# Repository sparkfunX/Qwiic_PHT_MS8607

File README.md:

# Qwiic PHT Sensor MS8607

The TE MS8607 combined pressure, humidity and temperature sensor in Qwiic format.

[Qwiic PHT Sensor MS8607 (SPX-16298)](https://www.sparkfun.com/products/16298)

The MS8607 sensor is a self-contained pressure, humidity and temperature sensor that is fully calibrated during manufacture.
The sensor can operate from 1.5V to 3.6V. The MS8607 is ideal for weather station applications embedded into compact devices and
any applications in which pressure, humidity and temperature monitoring is required. The pressure sensor will operate down to
10mbar which is equivalent to an altitude of approx. 31,000m making it suitable for high altitude ballooning and other low pressure
applications.

## Specifications

- Operating pressure range: 10 to 2000 mbar
- Measures relative humidity from 0% to 100%
- Measures temperature from -40C to 85C
- Fast response time
- I2C communication
- Very low power consumption

## Repository Contents
- **/Hardware** - Eagle schematic and PCB design files
- **/Documents** - contains the TE datasheet
- **LICENSE.md** contains the licence information

## Library

- **[Arduino Library](https://github.com/sparkfun/SparkFun_PHT_MS8607_Arduino_Library)** - Library for reading pressure in mBar, altitude, etc.

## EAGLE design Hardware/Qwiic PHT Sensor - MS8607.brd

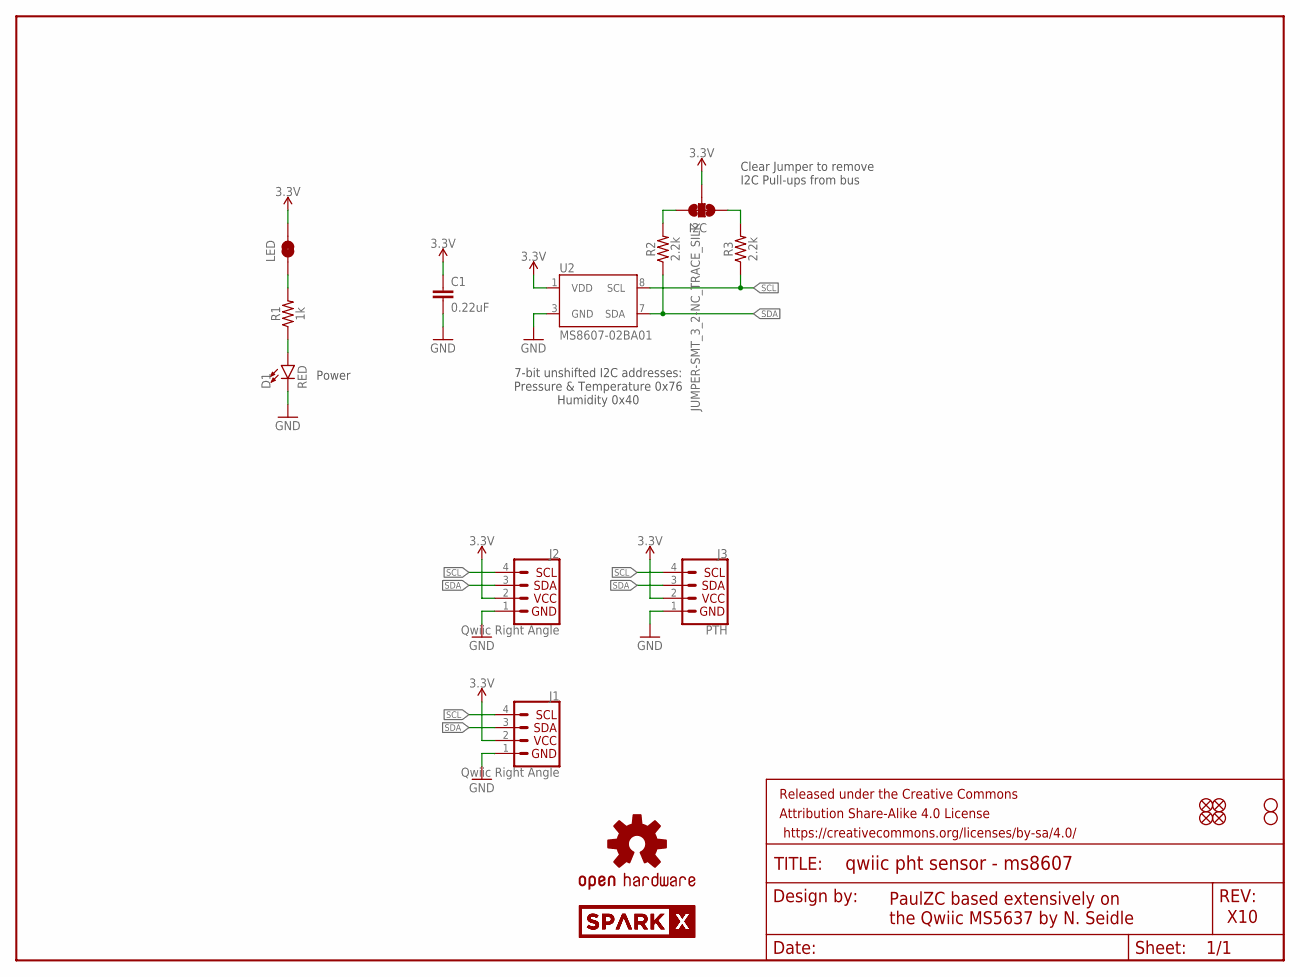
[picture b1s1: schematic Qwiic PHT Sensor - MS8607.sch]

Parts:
C1: 0.22uF; 0603
D1: RED; LED-0603
FRAME1: FRAME-LETTER; CREATIVE_COMMONS
I2C: JUMPER-SMT_3_2-NC_TRACE_SILK; SMT-JUMPER_3_2-NC_TRACE_SILK
J1, J2: Qwiic Right Angle; JST04_1MM_RA
J3: PTH; 1X04_NO_SILK
JP1, JP2, JP5, JP6: FIDUCIALUFIDUCIAL; MICRO-FIDUCIAL
JP3, JP4: STAND-OFF
LED: JUMPER-SMT_2_NC_TRACE_SILK; SMT-JUMPER_2_NC_TRACE_SILK
LOGO1: OSHW-LOGOMINI; OSHW-LOGO-MINI
R1: 1k; 0603
R2, R3: 2.2k; 0603
U2: MS8607-02BA01
U$1, U$2: SPARKX-LOGO4; SPARKX-MEDIUM

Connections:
3.3V: C1.1, I2C.2, J1.2, J2.2, J3.2 (VCC), LED.2, U2.1 (VDD)
GND: C1.2, D1.C, J1.1, J2.1, J3.1 (GND), U2.3 (GND)
unnamed: I2C.1, R3.2
unnamed: I2C.3, R2.2
unnamed: D1.A, R1.1
unnamed: LED.1, R1.2
SCL: J1.4, J2.4, J3.4 (SCL), R3.1, U2.8 (SCL)
SDA: J1.3, J2.3, J3.3 (SDA), R2.1, U2.7 (SDA)

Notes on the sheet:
PaulZC based extensively on the Qwiic MS5637 by N. Seidle
X10
7-bit unshifted I2C addresses: Pressure & Temperature 0x76 Humidity 0x40
Clear Jumper to remove I2C Pull-ups from bus
Power

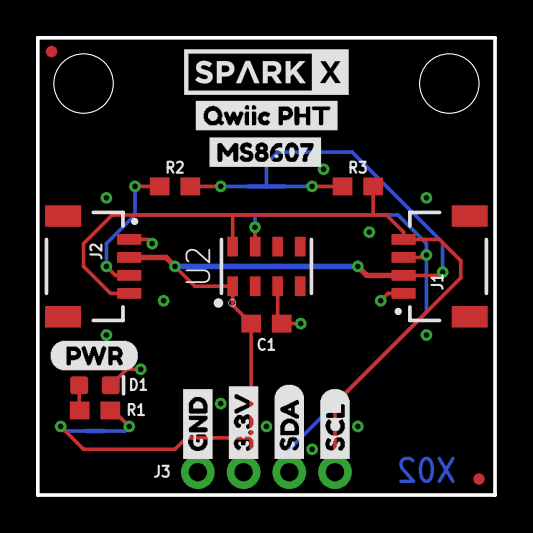
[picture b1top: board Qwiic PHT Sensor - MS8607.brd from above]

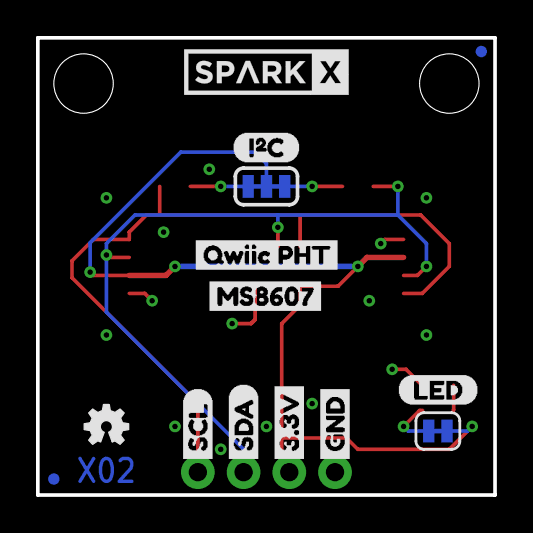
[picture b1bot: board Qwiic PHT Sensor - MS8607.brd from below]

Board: 2 copper layers, 25.4 x 25.4 mm, 36 parts (14 on the bottom side), 8 nets.

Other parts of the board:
U$3, U$22: GND1
U$4, U$21: 3#3V2
U$5, U$27: SDA8
U$6, U$26: SCL9
U$9, U$12: QWIIC_PHT0
U$10: (PWR)
U$11: (I_SUPER2_C)
U$15, U$16: MS86070
U$17: LED0

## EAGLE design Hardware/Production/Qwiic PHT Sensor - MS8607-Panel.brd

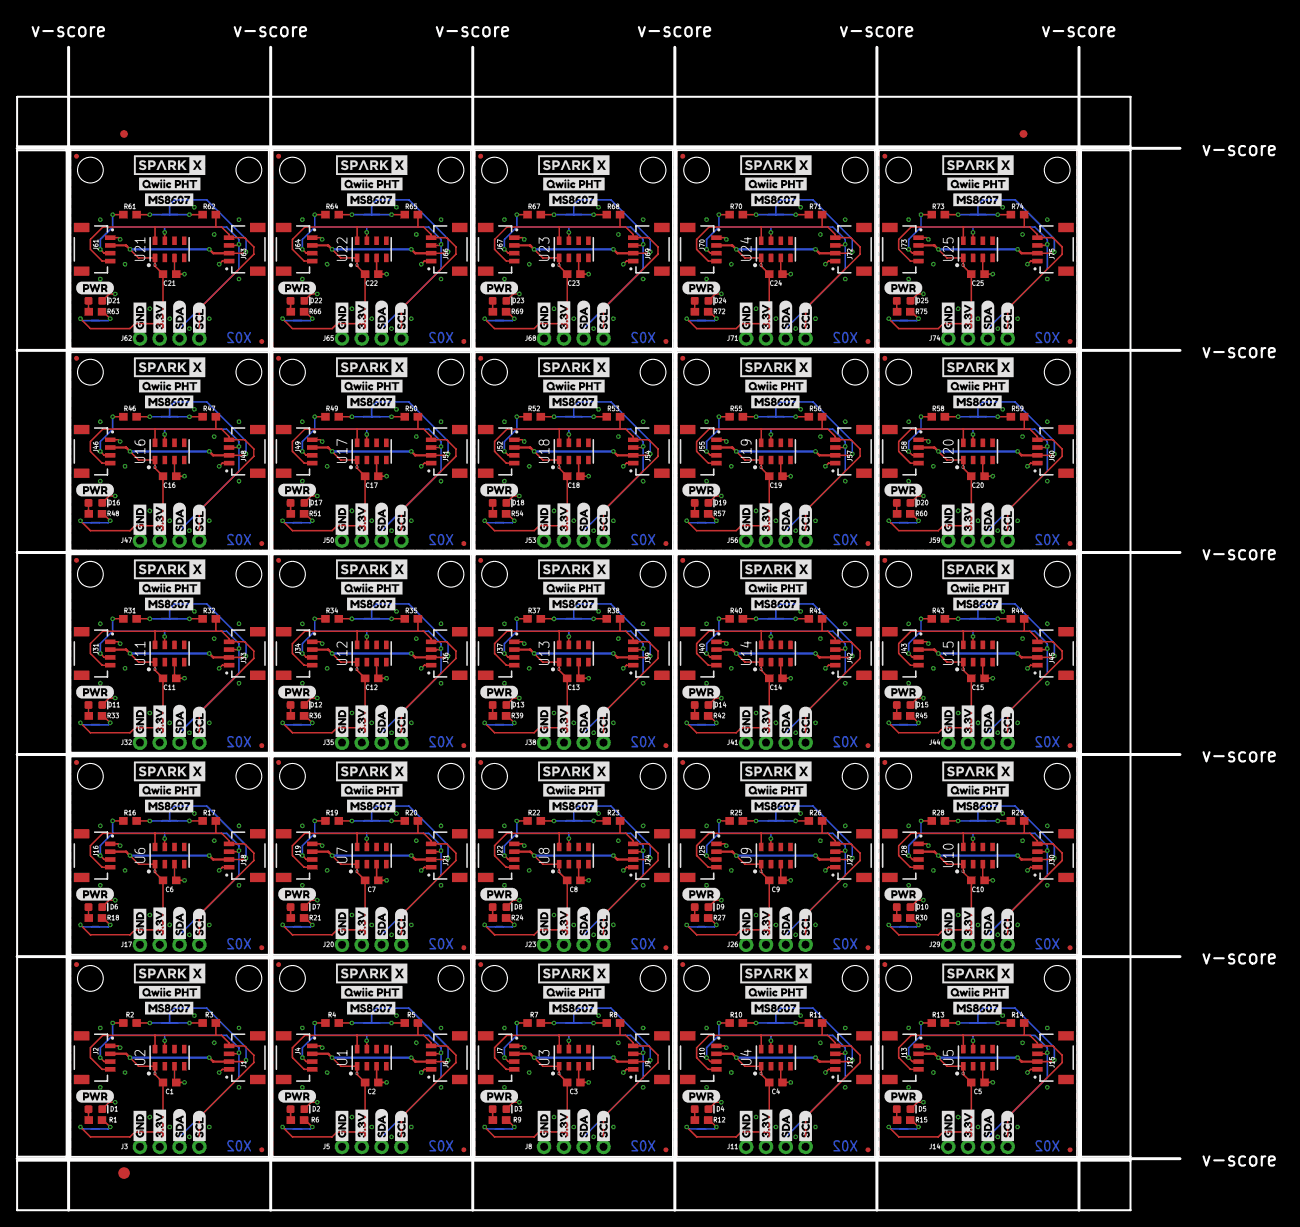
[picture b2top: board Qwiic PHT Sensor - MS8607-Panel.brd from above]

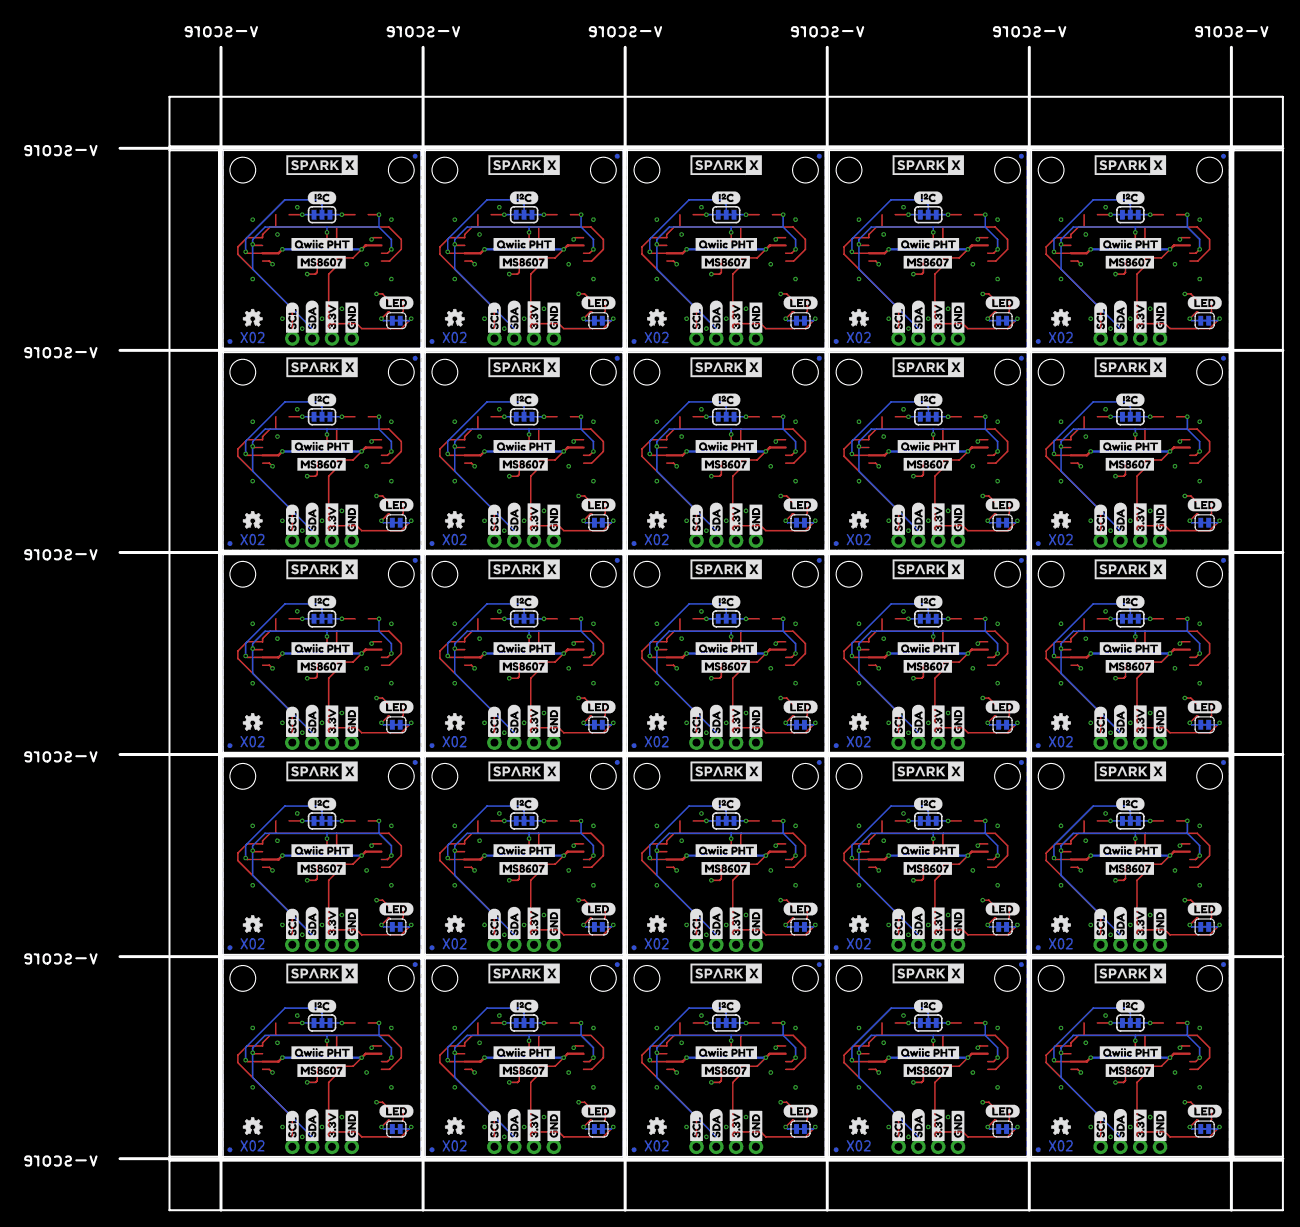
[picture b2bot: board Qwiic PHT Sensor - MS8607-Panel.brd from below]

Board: 2 copper layers, 162.3 x 153.0 mm, 878 parts (350 on the bottom side), 200 nets.

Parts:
C1, C2, C3, C4, C5, C6, C7, C8, C9, C10, C11, C12, C13, C14, C15, C16, C17, C18, C19, C20, C21, C22, C23, C24, C25: 0.22uF; 0603
D1, D2, D3, D4, D5, D6, D7, D8, D9, D10, D11, D12, D13, D14, D15, D16, D17, D18, D19, D20, D21, D22, D23, D24, D25: RED; LED-0603
E$1, E$2: FIDUCIAL-1X2
E$3: FIDUCIAL-1.5X3
I2C, I2C1, I2C2, I2C3, I2C4, I2C5, I2C6, I2C7, I2C8, I2C9, I2C10, I2C11, I2C12, I2C13, I2C14, I2C15, I2C16, I2C17, I2C18, I2C19, I2C20, I2C21, I2C22, I2C23, I2C24: JUMPER-SMT_3_2-NC_TRACE_SILK; SMT-JUMPER_3_2-NC_TRACE_SILK
J1, J2, J4, J6, J7, J9, J10, J12, J13, J15, J16, J18, J19, J21, J22, J24, J25, J27, J28, J30, J31, J33, J34, J36, J37, J39, J40, J42, J43, J45, J46, J48, J49, J51, J52, J54, J55, J57, J58, J60, J61, J63, J64, J66, J67, J69, J70, J72, J73, J75: Qwiic Right Angle; JST04_1MM_RA
J3, J5, J8, J11, J14, J17, J20, J23, J26, J29, J32, J35, J38, J41, J44, J47, J50, J53, J56, J59, J62, J65, J68, J71, J74: PTH; 1X04_NO_SILK
JP1, JP2, JP5, JP6, JP9, JP10, JP11, JP12, JP15, JP16, JP17, JP18, JP21, JP22, JP23, JP24, JP27, JP28, JP29, JP30, JP33, JP34, JP35, JP36, JP39, JP40, JP41, JP42, JP45, JP46, JP47, JP48, JP51, JP52, JP53, JP54, JP57, JP58, JP59, JP60, JP63, JP64, JP65, JP66, JP69, JP70, JP71, JP72, JP75, JP76, JP77, JP78, JP81, JP82, JP83, JP84, JP87, JP88, JP89, JP90, JP93, JP94, JP95, JP96, JP99, JP100, JP101, JP102, JP105, JP106, JP107, JP108, JP111, JP112, JP113, JP114, JP117, JP118, JP119, JP120, JP123, JP124, JP125, JP126, JP129, JP130, JP131, JP132, JP135, JP136, JP137, JP138, JP141, JP142, JP143, JP144, JP147, JP148, JP149, JP150: FIDUCIALUFIDUCIAL; MICRO-FIDUCIAL
JP3, JP4, JP7, JP8, JP13, JP14, JP19, JP20, JP25, JP26, JP31, JP32, JP37, JP38, JP43, JP44, JP49, JP50, JP55, JP56, JP61, JP62, JP67, JP68, JP73, JP74, JP79, JP80, JP85, JP86, JP91, JP92, JP97, JP98, JP103, JP104, JP109, JP110, JP115, JP116, JP121, JP122, JP127, JP128, JP133, JP134, JP139, JP140, JP145, JP146: STAND-OFF
LED, LED1, LED2, LED3, LED4, LED5, LED6, LED7, LED8, LED9, LED10, LED11, LED12, LED13, LED14, LED15, LED16, LED17, LED18, LED19, LED20, LED21, LED22, LED23, LED24: JUMPER-SMT_2_NC_TRACE_SILK; SMT-JUMPER_2_NC_TRACE_SILK
LOGO1, LOGO2, LOGO3, LOGO4, LOGO5, LOGO6, LOGO7, LOGO8, LOGO9, LOGO10, LOGO11, LOGO12, LOGO13, LOGO14, LOGO15, LOGO16, LOGO17, LOGO18, LOGO19, LOGO20, LOGO21, LOGO22, LOGO23, LOGO24, LOGO25: OSHW-LOGOMINI; OSHW-LOGO-MINI
R1, R6, R9, R12, R15, R18, R21, R24, R27, R30, R33, R36, R39, R42, R45, R48, R51, R54, R57, R60, R63, R66, R69, R72, R75: 1k; 0603
R2, R3, R4, R5, R7, R8, R10, R11, R13, R14, R16, R17, R19, R20, R22, R23, R25, R26, R28, R29, R31, R32, R34, R35, R37, R38, R40, R41, R43, R44, R46, R47, R49, R50, R52, R53, R55, R56, R58, R59, R61, R62, R64, R65, R67, R68, R70, R71, R73, R74: 2.2k; 0603
U1, U2, U3, U4, U5, U6, U7, U8, U9, U10, U11, U12, U13, U14, U15, U16, U17, U18, U19, U20, U21, U22, U23, U24, U25: MS8607-02BA01
U$1, U$2, U$7, U$8, U$35, U$36, U$52, U$53, U$69, U$70, U$86, U$87, U$103, U$104, U$120, U$121, U$137, U$138, U$154, U$155, U$171, U$172, U$188, U$189, U$205, U$206, U$222, U$223, U$239, U$240, U$256, U$257, U$273, U$274, U$290, U$291, U$307, U$308, U$324, U$325, U$341, U$342, U$358, U$359, U$375, U$376, U$392, U$393, U$409, U$410: SPARKX-LOGO4; SPARKX-MEDIUM
U$3, U$14, U$20, U$22, U$38, U$41, U$55, U$58, U$72, U$75, U$89, U$92, U$106, U$109, U$123, U$126, U$140, U$143, U$157, U$160, U$174, U$177, U$191, U$194, U$208, U$211, U$225, U$228, U$242, U$245, U$259, U$262, U$276, U$279, U$293, U$296, U$310, U$313, U$327, U$330, U$344, U$347, U$361, U$364, U$378, U$381, U$395, U$398, U$412, U$415: GND1
U$4, U$13, U$21, U$23, U$37, U$42, U$54, U$59, U$71, U$76, U$88, U$93, U$105, U$110, U$122, U$127, U$139, U$144, U$156, U$161, U$173, U$178, U$190, U$195, U$207, U$212, U$224, U$229, U$241, U$246, U$258, U$263, U$275, U$280, U$292, U$297, U$309, U$314, U$326, U$331, U$343, U$348, U$360, U$365, U$377, U$382, U$394, U$399, U$411, U$416: 3#3V2
U$5, U$19, U$24, U$27, U$40, U$43, U$57, U$60, U$74, U$77, U$91, U$94, U$108, U$111, U$125, U$128, U$142, U$145, U$159, U$162, U$176, U$179, U$193, U$196, U$210, U$213, U$227, U$230, U$244, U$247, U$261, U$264, U$278, U$281, U$295, U$298, U$312, U$315, U$329, U$332, U$346, U$349, U$363, U$366, U$380, U$383, U$397, U$400, U$414, U$417: SDA8
U$6, U$18, U$25, U$26, U$39, U$44, U$56, U$61, U$73, U$78, U$90, U$95, U$107, U$112, U$124, U$129, U$141, U$146, U$158, U$163, U$175, U$180, U$192, U$197, U$209, U$214, U$226, U$231, U$243, U$248, U$260, U$265, U$277, U$282, U$294, U$299, U$311, U$316, U$328, U$333, U$345, U$350, U$362, U$367, U$379, U$384, U$396, U$401, U$413, U$418: SCL9
U$9, U$12, U$30, U$31, U$47, U$48, U$64, U$65, U$81, U$82, U$98, U$99, U$115, U$116, U$132, U$133, U$149, U$150, U$166, U$167, U$183, U$184, U$200, U$201, U$217, U$218, U$234, U$235, U$251, U$252, U$268, U$269, U$285, U$286, U$302, U$303, U$319, U$320, U$336, U$337, U$353, U$354, U$370, U$371, U$387, U$388, U$404, U$405, U$421, U$422: QWIIC_PHT0
U$10, U$28, U$45, U$62, U$79, U$96, U$113, U$130, U$147, U$164, U$181, U$198, U$215, U$232, U$249, U$266, U$283, U$300, U$317, U$334, U$351, U$368, U$385, U$402, U$419: (PWR)
U$11, U$29, U$46, U$63, U$80, U$97, U$114, U$131, U$148, U$165, U$182, U$199, U$216, U$233, U$250, U$267, U$284, U$301, U$318, U$335, U$352, U$369, U$386, U$403, U$420: (I_SUPER2_C)
U$15, U$16, U$32, U$33, U$49, U$50, U$66, U$67, U$83, U$84, U$100, U$101, U$117, U$118, U$134, U$135, U$151, U$152, U$168, U$169, U$185, U$186, U$202, U$203, U$219, U$220, U$236, U$237, U$253, U$254, U$270, U$271, U$287, U$288, U$304, U$305, U$321, U$322, U$338, U$339, U$355, U$356, U$372, U$373, U$389, U$390, U$406, U$407, U$423, U$424: MS86070
U$17, U$34, U$51, U$68, U$85, U$102, U$119, U$136, U$153, U$170, U$187, U$204, U$221, U$238, U$255, U$272, U$289, U$306, U$323, U$340, U$357, U$374, U$391, U$408, U$425: LED0

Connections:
3.3V: C1.1, I2C.2, J1.2, J2.2, J3.2, LED.2, U2.1
3.3V1: C2.1, I2C1.2, J4.2, J5.2, J6.2, LED1.2, U1.1
3.3V2: C3.1, I2C2.2, J7.2, J8.2, J9.2, LED2.2, U3.1
3.3V3: C4.1, I2C3.2, J10.2, J11.2, J12.2, LED3.2, U4.1
3.3V4: C5.1, I2C4.2, J13.2, J14.2, J15.2, LED4.2, U5.1
3.3V5: C6.1, I2C5.2, J16.2, J17.2, J18.2, LED5.2, U6.1
3.3V6: C7.1, I2C6.2, J19.2, J20.2, J21.2, LED6.2, U7.1
3.3V7: C8.1, I2C7.2, J22.2, J23.2, J24.2, LED7.2, U8.1
3.3V8: C9.1, I2C8.2, J25.2, J26.2, J27.2, LED8.2, U9.1
3.3V9: C10.1, I2C9.2, J28.2, J29.2, J30.2, LED9.2, U10.1
3.3V10: C11.1, I2C10.2, J31.2, J32.2, J33.2, LED10.2, U11.1
3.3V11: C12.1, I2C11.2, J34.2, J35.2, J36.2, LED11.2, U12.1
3.3V12: C13.1, I2C12.2, J37.2, J38.2, J39.2, LED12.2, U13.1
3.3V13: C14.1, I2C13.2, J40.2, J41.2, J42.2, LED13.2, U14.1
3.3V14: C15.1, I2C14.2, J43.2, J44.2, J45.2, LED14.2, U15.1
3.3V15: C16.1, I2C15.2, J46.2, J47.2, J48.2, LED15.2, U16.1
3.3V16: C17.1, I2C16.2, J49.2, J50.2, J51.2, LED16.2, U17.1
3.3V17: C18.1, I2C17.2, J52.2, J53.2, J54.2, LED17.2, U18.1
3.3V18: C19.1, I2C18.2, J55.2, J56.2, J57.2, LED18.2, U19.1
3.3V19: C20.1, I2C19.2, J58.2, J59.2, J60.2, LED19.2, U20.1
3.3V20: C21.1, I2C20.2, J61.2, J62.2, J63.2, LED20.2, U21.1
3.3V21: C22.1, I2C21.2, J64.2, J65.2, J66.2, LED21.2, U22.1
3.3V22: C23.1, I2C22.2, J67.2, J68.2, J69.2, LED22.2, U23.1
3.3V23: C24.1, I2C23.2, J70.2, J71.2, J72.2, LED23.2, U24.1
3.3V24: C25.1, I2C24.2, J73.2, J74.2, J75.2, LED24.2, U25.1
GND: C1.2, D1.C, J1.1, J2.1, J3.1, U2.3
GND1: C2.2, D2.C, J4.1, J5.1, J6.1, U1.3
GND2: C3.2, D3.C, J7.1, J8.1, J9.1, U3.3
GND3: C4.2, D4.C, J10.1, J11.1, J12.1, U4.3
GND4: C5.2, D5.C, J13.1, J14.1, J15.1, U5.3
GND5: C6.2, D6.C, J16.1, J17.1, J18.1, U6.3
GND6: C7.2, D7.C, J19.1, J20.1, J21.1, U7.3
GND7: C8.2, D8.C, J22.1, J23.1, J24.1, U8.3
GND8: C9.2, D9.C, J25.1, J26.1, J27.1, U9.3
GND9: C10.2, D10.C, J28.1, J29.1, J30.1, U10.3
GND10: C11.2, D11.C, J31.1, J32.1, J33.1, U11.3
GND11: C12.2, D12.C, J34.1, J35.1, J36.1, U12.3
GND12: C13.2, D13.C, J37.1, J38.1, J39.1, U13.3
GND13: C14.2, D14.C, J40.1, J41.1, J42.1, U14.3
GND14: C15.2, D15.C, J43.1, J44.1, J45.1, U15.3
GND15: C16.2, D16.C, J46.1, J47.1, J48.1, U16.3
GND16: C17.2, D17.C, J49.1, J50.1, J51.1, U17.3
GND17: C18.2, D18.C, J52.1, J53.1, J54.1, U18.3
GND18: C19.2, D19.C, J55.1, J56.1, J57.1, U19.3
GND19: C20.2, D20.C, J58.1, J59.1, J60.1, U20.3
GND20: C21.2, D21.C, J61.1, J62.1, J63.1, U21.3
GND21: C22.2, D22.C, J64.1, J65.1, J66.1, U22.3
GND22: C23.2, D23.C, J67.1, J68.1, J69.1, U23.3
GND23: C24.2, D24.C, J70.1, J71.1, J72.1, U24.3
GND24: C25.2, D25.C, J73.1, J74.1, J75.1, U25.3
unnamed: I2C.1, R3.2
unnamed: I2C.3, R2.2
unnamed: D1.A, R1.1
unnamed: LED.1, R1.2
unnamed: I2C1.1, R5.2
unnamed: I2C1.3, R4.2
unnamed: D2.A, R6.1
unnamed: LED1.1, R6.2
unnamed: I2C2.1, R8.2
unnamed: I2C2.3, R7.2
unnamed: D3.A, R9.1
unnamed: LED2.1, R9.2
unnamed: I2C3.1, R11.2
unnamed: I2C3.3, R10.2
unnamed: D4.A, R12.1
unnamed: LED3.1, R12.2
unnamed: I2C4.1, R14.2
unnamed: I2C4.3, R13.2
unnamed: D5.A, R15.1
unnamed: LED4.1, R15.2
unnamed: I2C5.1, R17.2
unnamed: I2C5.3, R16.2
unnamed: D6.A, R18.1
unnamed: LED5.1, R18.2
unnamed: I2C6.1, R20.2
unnamed: I2C6.3, R19.2
unnamed: D7.A, R21.1
unnamed: LED6.1, R21.2
unnamed: I2C7.1, R23.2
unnamed: I2C7.3, R22.2
unnamed: D8.A, R24.1
unnamed: LED7.1, R24.2
unnamed: I2C8.1, R26.2
unnamed: I2C8.3, R25.2
unnamed: D9.A, R27.1
unnamed: LED8.1, R27.2
unnamed: I2C9.1, R29.2
unnamed: I2C9.3, R28.2
unnamed: D10.A, R30.1
unnamed: LED9.1, R30.2
unnamed: I2C10.1, R32.2
unnamed: I2C10.3, R31.2
unnamed: D11.A, R33.1
unnamed: LED10.1, R33.2
unnamed: I2C11.1, R35.2
unnamed: I2C11.3, R34.2
unnamed: D12.A, R36.1
unnamed: LED11.1, R36.2
unnamed: I2C12.1, R38.2
unnamed: I2C12.3, R37.2
unnamed: D13.A, R39.1
unnamed: LED12.1, R39.2
unnamed: I2C13.1, R41.2
unnamed: I2C13.3, R40.2
unnamed: D14.A, R42.1
unnamed: LED13.1, R42.2
unnamed: I2C14.1, R44.2
unnamed: I2C14.3, R43.2
unnamed: D15.A, R45.1
unnamed: LED14.1, R45.2
unnamed: I2C15.1, R47.2
unnamed: I2C15.3, R46.2
unnamed: D16.A, R48.1
unnamed: LED15.1, R48.2
unnamed: I2C16.1, R50.2
unnamed: I2C16.3, R49.2
unnamed: D17.A, R51.1
unnamed: LED16.1, R51.2
unnamed: I2C17.1, R53.2
unnamed: I2C17.3, R52.2
unnamed: D18.A, R54.1
unnamed: LED17.1, R54.2
unnamed: I2C18.1, R56.2
unnamed: I2C18.3, R55.2
unnamed: D19.A, R57.1
unnamed: LED18.1, R57.2
unnamed: I2C19.1, R59.2
unnamed: I2C19.3, R58.2
unnamed: D20.A, R60.1
unnamed: LED19.1, R60.2
unnamed: I2C20.1, R62.2
unnamed: I2C20.3, R61.2
unnamed: D21.A, R63.1
unnamed: LED20.1, R63.2
unnamed: I2C21.1, R65.2
unnamed: I2C21.3, R64.2
unnamed: D22.A, R66.1
unnamed: LED21.1, R66.2
unnamed: I2C22.1, R68.2
unnamed: I2C22.3, R67.2
unnamed: D23.A, R69.1
unnamed: LED22.1, R69.2
unnamed: I2C23.1, R71.2
unnamed: I2C23.3, R70.2
unnamed: D24.A, R72.1
unnamed: LED23.1, R72.2
unnamed: I2C24.1, R74.2
unnamed: I2C24.3, R73.2
unnamed: D25.A, R75.1
unnamed: LED24.1, R75.2
SCL: J1.4, J2.4, J3.4, R3.1, U2.8
SCL1: J4.4, J5.4, J6.4, R5.1, U1.8
SCL2: J7.4, J8.4, J9.4, R8.1, U3.8
SCL3: J10.4, J11.4, J12.4, R11.1, U4.8
SCL4: J13.4, J14.4, J15.4, R14.1, U5.8
SCL5: J16.4, J17.4, J18.4, R17.1, U6.8
SCL6: J19.4, J20.4, J21.4, R20.1, U7.8
SCL7: J22.4, J23.4, J24.4, R23.1, U8.8
SCL8: J25.4, J26.4, J27.4, R26.1, U9.8
SCL9: J28.4, J29.4, J30.4, R29.1, U10.8
SCL10: J31.4, J32.4, J33.4, R32.1, U11.8
SCL11: J34.4, J35.4, J36.4, R35.1, U12.8
SCL12: J37.4, J38.4, J39.4, R38.1, U13.8
SCL13: J40.4, J41.4, J42.4, R41.1, U14.8
SCL14: J43.4, J44.4, J45.4, R44.1, U15.8
SCL15: J46.4, J47.4, J48.4, R47.1, U16.8
SCL16: J49.4, J50.4, J51.4, R50.1, U17.8
SCL17: J52.4, J53.4, J54.4, R53.1, U18.8
SCL18: J55.4, J56.4, J57.4, R56.1, U19.8
SCL19: J58.4, J59.4, J60.4, R59.1, U20.8
SCL20: J61.4, J62.4, J63.4, R62.1, U21.8
SCL21: J64.4, J65.4, J66.4, R65.1, U22.8
SCL22: J67.4, J68.4, J69.4, R68.1, U23.8
SCL23: J70.4, J71.4, J72.4, R71.1, U24.8
SCL24: J73.4, J74.4, J75.4, R74.1, U25.8
SDA: J1.3, J2.3, J3.3, R2.1, U2.7
SDA1: J4.3, J5.3, J6.3, R4.1, U1.7
SDA2: J7.3, J8.3, J9.3, R7.1, U3.7
SDA3: J10.3, J11.3, J12.3, R10.1, U4.7
SDA4: J13.3, J14.3, J15.3, R13.1, U5.7
SDA5: J16.3, J17.3, J18.3, R16.1, U6.7
SDA6: J19.3, J20.3, J21.3, R19.1, U7.7
SDA7: J22.3, J23.3, J24.3, R22.1, U8.7
SDA8: J25.3, J26.3, J27.3, R25.1, U9.7
SDA9: J28.3, J29.3, J30.3, R28.1, U10.7
SDA10: J31.3, J32.3, J33.3, R31.1, U11.7
SDA11: J34.3, J35.3, J36.3, R34.1, U12.7
SDA12: J37.3, J38.3, J39.3, R37.1, U13.7
SDA13: J40.3, J41.3, J42.3, R40.1, U14.7
SDA14: J43.3, J44.3, J45.3, R43.1, U15.7
SDA15: J46.3, J47.3, J48.3, R46.1, U16.7
SDA16: J49.3, J50.3, J51.3, R49.1, U17.7
SDA17: J52.3, J53.3, J54.3, R52.1, U18.7
SDA18: J55.3, J56.3, J57.3, R55.1, U19.7
SDA19: J58.3, J59.3, J60.3, R58.1, U20.7
SDA20: J61.3, J62.3, J63.3, R61.1, U21.7
SDA21: J64.3, J65.3, J66.3, R64.1, U22.7
SDA22: J67.3, J68.3, J69.3, R67.1, U23.7
SDA23: J70.3, J71.3, J72.3, R70.1, U24.7
SDA24: J73.3, J74.3, J75.3, R73.1, U25.7

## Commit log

2020-05-13 Copying across PaulZC/Qwiic_PHT_MS8607 and sparkfunx/Qwiic_PHT_MS8607
2020-05-15 Added product link

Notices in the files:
parts and their libraries:
SparkFun-Resistors: Licensing: Creative Commons ShareAlike 4.0 International - https://creativecommons.org/licenses/by-sa/4.0
SparkFun-Aesthetics: Released under the Creative Commons Attribution Share-Alike 4.0 License
SparkFun-Aesthetics: https://creativecommons.org/licenses/by-sa/4.0
